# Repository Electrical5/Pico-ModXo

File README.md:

# Pi Pico modchip adapter for Original Xbox

This version is based on the ['V1 version'](https://github.com/Team-Resurgent/Modxo) by Team Resurgent (including Shalx)

See the [V0.2 release](https://github.com/Electrical5/Pico-ModXo/releases/tag/V0.2) for the support of the original "[ModXo](https://github.com/shalxmva/modxo)" by Shalx

# Easy to solder

All components can be soldered 'though hole' at home and the Pico/resistors also have 'surface mount' options, making it ideal for hobbyists or mass production.

# Fully open source

The KiCad (free application) source files (full schematics!) are included, so you can add/remove components based on your preferences.

# SMBus

Currently ModXo doesn't implement reading SMBus via I2C, in the future this could add functionality such as monitoring temperature/fanspeed, LED control or restarting/shutdown the xbox remotely.
Especially if paired with the Pi Pico Wireless, it could allow basic remote control / monitoring of the xbox.
However, there's two solder jumpers to connect the SMBus of the Xbox to the Pi Pico.

# License

GNU GENERAL PUBLIC LICENSE
Version 3, 29 June 2007

You can sell this board as-is, but disclose the source.
If you sell modifications of this board (additional headers for LED strips / LCD / fan), share the modifications / source files under the same license.

# More info

https://github.com/shalxmva/modxo
https://consolemods.org/wiki/Xbox:ModXo

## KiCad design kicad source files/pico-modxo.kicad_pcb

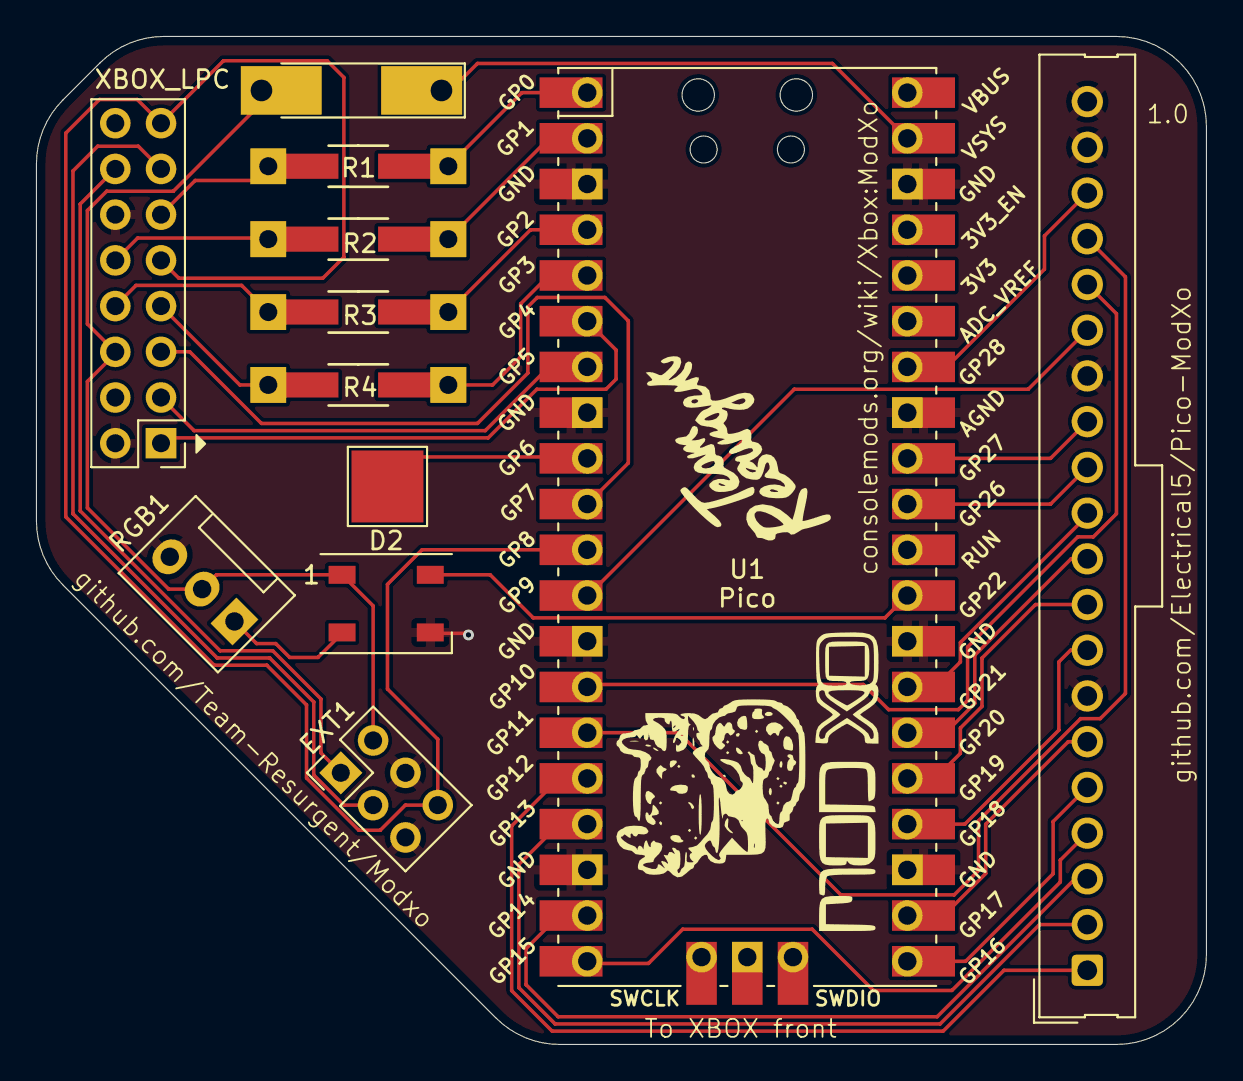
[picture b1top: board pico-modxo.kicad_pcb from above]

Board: 2 copper layers, 65.0 x 56.0 mm, 12 parts (0 on the bottom side), 36 nets.

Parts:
D0: D0 (V1.0-V1.5); TestPoint_Pad_4.0x4.0mm
D1: RB551VM-30TE-17; D_MELF-RM10_Universal_Handsoldering
D2: WS2812B; LED_WS2812B_PLCC4_5.0x5.0mm_P3.2mm
EXT1: Conn_02x03_Odd_Even; PinHeader_2x03_P2.54mm_Vertical
J1: XBOX_LPC; xbox_lpc
J2: H2; Molex_SL_171971-0020_1x20_P2.54mm_Vertical
R1, R2, R3, R4: 100Ω; Resistor_SMD+THTuniversal_1206_RM10_HandSoldering
RGB1: RGB1; FanPinHeader_1x03_P2.54mm_Vertical
U1: Pico; RPi_Pico_SMD_TH

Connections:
+3.3V: EXT1.6, J1.9 (3.3V), J1.15 (3.3V), U1.11 (GPIO8)
+5V: D1.1 (K), U1.39 (VSYS)
DISPLAY_BRIGHTNESS: J2.12, U1.31 (GPIO26_ADC0)
DISPLAY_CONTRAST: J2.13, U1.32 (GPIO27_ADC1)
DISPLAY_I2C1_SCL: J2.9, U1.25 (GPIO19)
DISPLAY_I2C1_SDA: J2.8, U1.24 (GPIO18)
EXT_I2C0_SCL: J2.11, U1.27 (GPIO21)
EXT_I2C0_SDA: J2.10, U1.26 (GPIO20)
GND: D2.3 (VSS), EXT1.4, EXT1.5, J1.2 (GND), J1.12 (GND), J2.7, J2.14, J2.19, J2.20, RGB1.3, U1.3 (GND), U1.8 (GND), U1.13 (GND), U1.18 (GND), U1.23 (GND), U1.28 (GND), U1.33 (AGND), U1.38 (GND)
GPIO9: J2.15, U1.12 (GPIO9)
GPIO10: J2.16, U1.14 (GPIO10)
GPIO11: J2.17, U1.15 (GPIO11)
GPIO28: J2.18, U1.34 (GPIO28_ADC2)
LAD0: J1.11 (LAD0), R1.1
LAD1: J1.10 (LAD1), R2.1
LAD2: J1.8 (LAD2), R3.1
LAD3: J1.7 (LAD3), R4.1
LCLK: J1.1 (LCLK), U1.6 (GPIO4)
LFRAME: J1.3 (LFRAME#), U1.7 (GPIO5)
LPC_5V: D1.2 (A), D2.1 (VDD), EXT1.2, J1.6 (5V), RGB1.2
LRESET: J1.5 (LRESET#), U1.10 (GPIO7)
LSCL: EXT1.3, J1.13 (SCL)
LSDA: EXT1.1, J1.14 (SDA)
unnamed: D0.1, U1.9 (GPIO6)
unnamed: D2.2 (DOUT), RGB1.1
unnamed: R1.2, U1.1 (GPIO0)
unnamed: R2.2, U1.2 (GPIO1)
unnamed: R3.2, U1.4 (GPIO2)
unnamed: R4.2, U1.5 (GPIO3)
RGBDI: D2.4 (DIN), U1.29 (GPIO22)
SD_SPI1_CS: J2.2, U1.17 (GPIO13)
SD_SPI1_MISO: J2.1, U1.16 (GPIO12)
SD_SPI1_MOSI: J2.4, U1.20 (GPIO15)
SD_SPI1_SCK: J2.3, U1.19 (GPIO14)
UART_RX: J2.6, U1.22 (GPIO17)
UART_TX: J2.5, U1.21 (GPIO16)

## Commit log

2024-07-28 Initial commit
    Initial commit
2024-07-28 Added schematics
2024-07-28 Create LICENSE
2024-08-18 V2 Design
    V2 Design based on EqUiNoX schematic 1.0 2024-07-29
2024-08-18 Updated board to V2
    See old 'V1' branch for original.
    This V2 branch has suppport for LED / GPIO etc.
2024-08-19 Move GND add GP8
    added Gp8 connected to 3.3v
    moved GND to bottom.
2024-08-19 RGB LED GND via
    added via to Grad plain for RGB LED
2024-08-19 Pico ModXo V1.0
    Release V1.0
